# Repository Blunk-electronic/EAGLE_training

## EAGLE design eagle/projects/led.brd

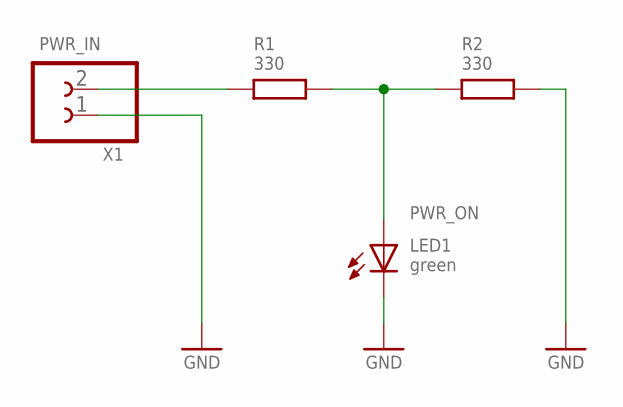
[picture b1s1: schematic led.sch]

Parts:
LED1: green; S_0805; PART_CODE_BEL LED_PAC_S_0805_VAL_green
R1, R2: 330; S_0805; PART_CODE_BEL R_PAC_S_0805_VAL_330
X1: CLAMP_1X2-T-2.5MM; T_WIRE_CLAMP_1X2_PITCH_2MM5

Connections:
GND: LED1.C, R2.2, X1.1
LED_A: LED1.A, R1.2, R2.1
PWR_IN: R1.1, X1.2

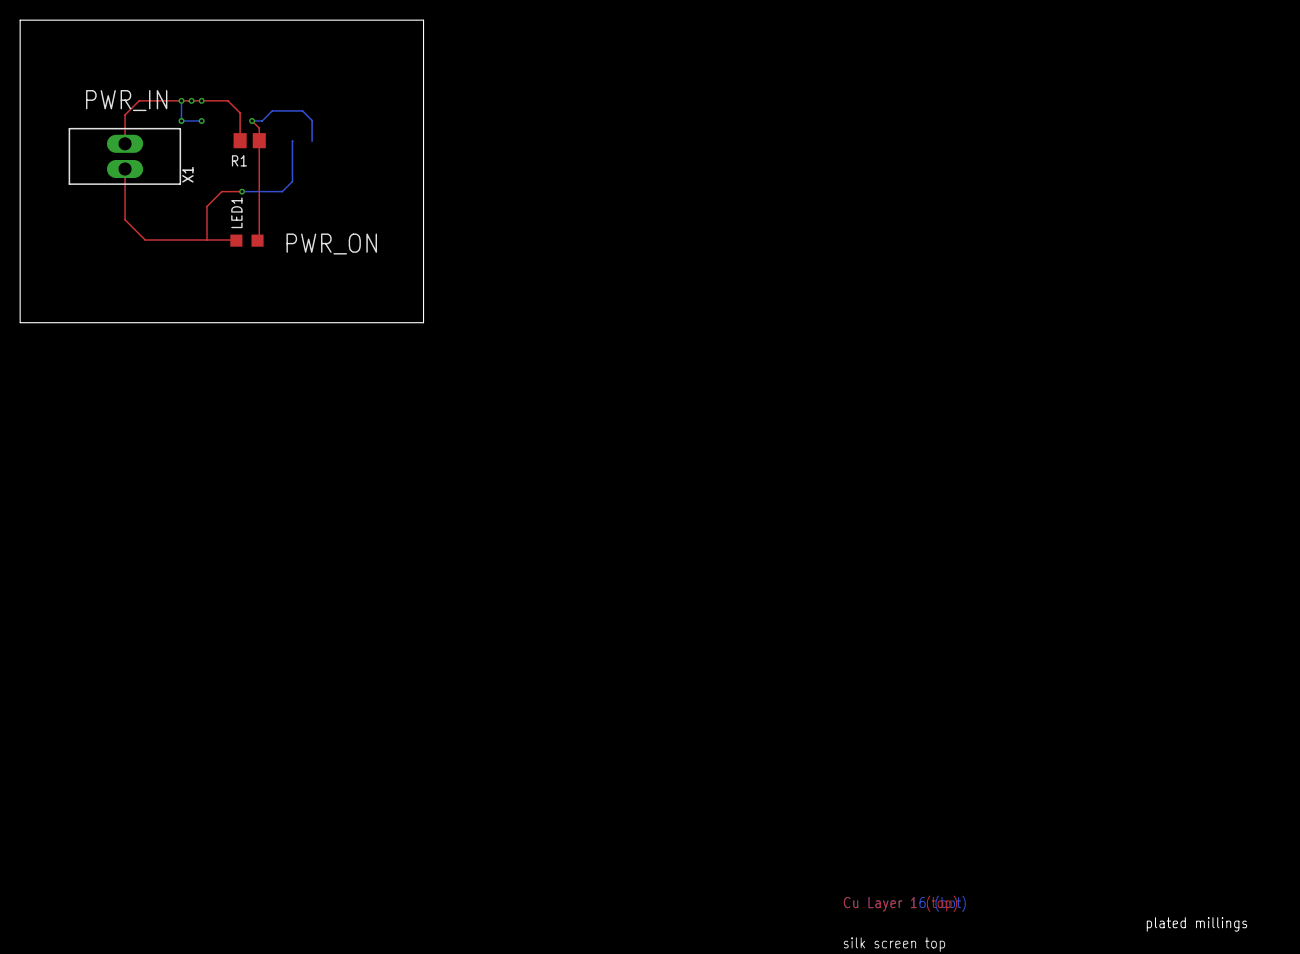
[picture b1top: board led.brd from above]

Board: 4 copper layers, 40.0 x 30.0 mm, 5 parts (1 on the bottom side), 3 nets.

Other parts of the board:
U$1: A4_LANDSCAPE

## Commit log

2019-01-11 simple led board
2019-01-29 Added an ignore-file in directory bom. This was the bom directory is always there on cloning.
2019-07-10 test buried vias
2019-07-11 improve ignore files
2019-07-11 added frame around layout
2019-07-11 ignore tide files
2019-07-12 test attributes
2019-08-27 change scriipt dir
2020-09-02 remove attribute trm
2020-09-26 clean up. remove obsolete stuff

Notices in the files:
parts and their libraries:
be_frame: Copyright(C) Blunk electronic
